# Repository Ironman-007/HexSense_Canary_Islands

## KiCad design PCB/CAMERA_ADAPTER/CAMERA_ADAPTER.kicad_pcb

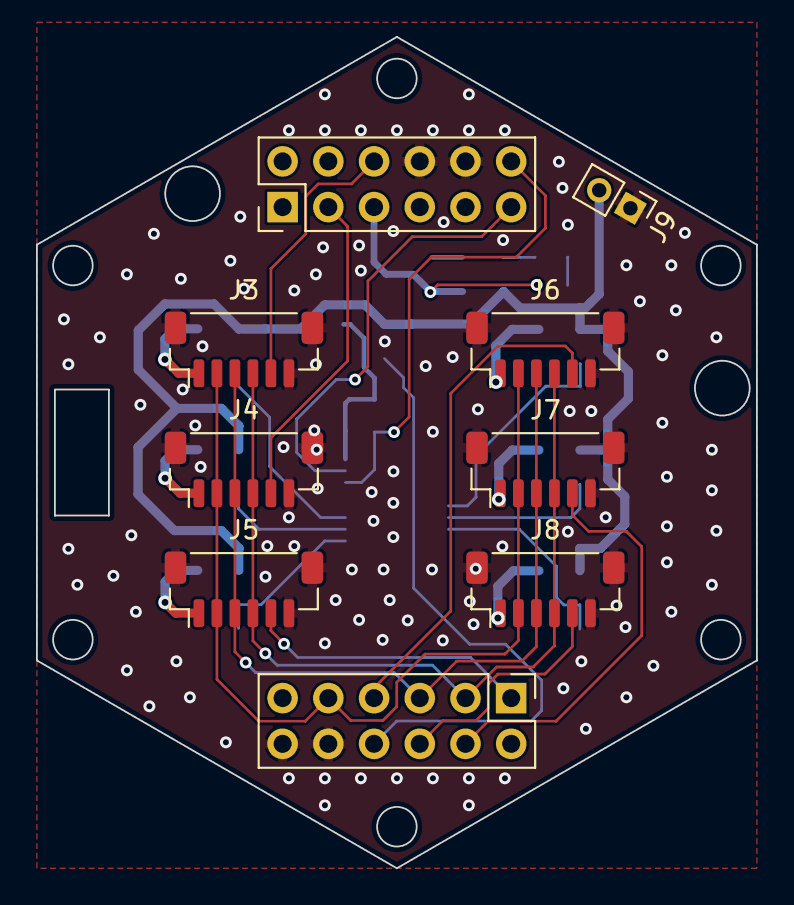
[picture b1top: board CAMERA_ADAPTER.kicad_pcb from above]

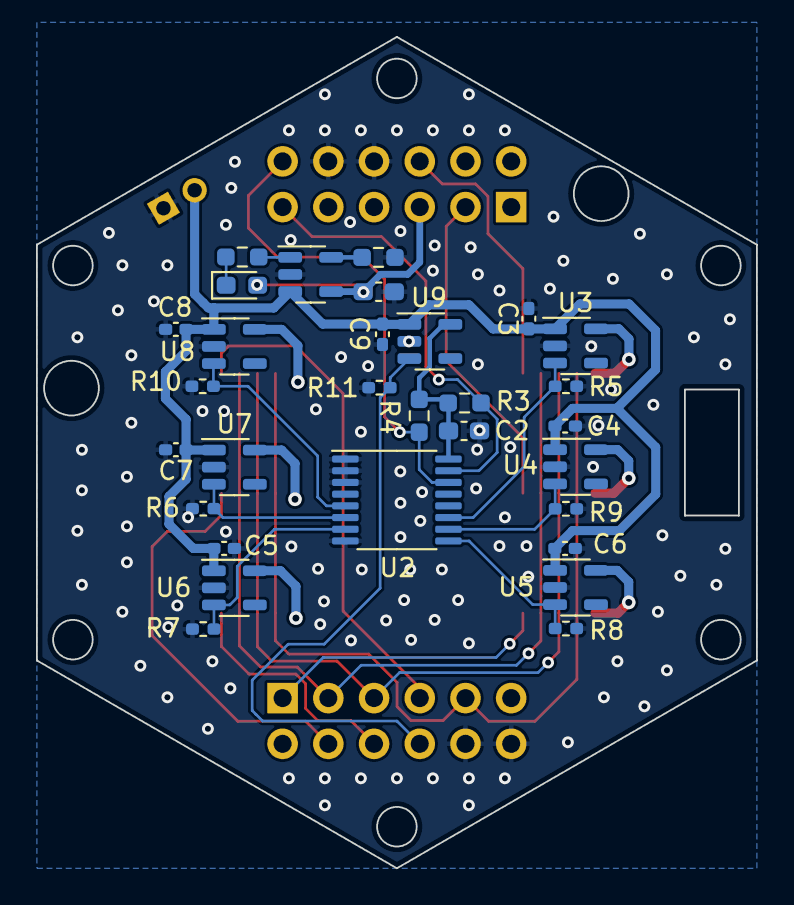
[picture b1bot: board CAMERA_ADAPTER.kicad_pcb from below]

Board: 2 copper layers, 40.0 x 46.2 mm, 39 parts (30 on the bottom side), 31 nets.

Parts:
C1, C2: 0.1uF; C_0603_1608Metric_Pad1.08x0.95mm_HandSolder
C3, C4, C5, C6, C7, C8, C9: 0.1uF; C_0402_1005Metric_Pad0.74x0.62mm_HandSolder
D1: RED; LED_0603_1608Metric_Pad1.05x0.95mm_HandSolder
J1, J2: Conn_02x06_Odd_Even; PinHeader_2x06_P2.54mm_Vertical
J3, J4, J5, J6, J7, J8: BM06B-SRSS-TBT(LF)(SN); JST_SH_BM06B-SRSS-TB_1x06-1MP_P1.00mm_Vertical
J9: Battery; PinHeader_1x02_P2.00mm_Vertical
R1: 10k; R_0603_1608Metric_Pad0.98x0.95mm_HandSolder
R2: 1k; R_0603_1608Metric_Pad0.98x0.95mm_HandSolder
R3, R4: NC; R_0603_1608Metric_Pad0.98x0.95mm_HandSolder
R5, R6, R7, R8, R9, R10, R11: 10k; R_0402_1005Metric_Pad0.72x0.64mm_HandSolder
U1: MCP73831-2-OT; SOT-23-5
U2: TCA9534; TSSOP-16_4.4x5mm_P0.65mm
U3, U4, U5, U6, U7, U8, U9: AP2112K-3.3; SOT-23-5

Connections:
+5V: C1.1, D1.2 (A), J1.5, U1.4 (VDD)
/A2: J1.6, J3.5
/A4: J2.8, R11.1, U9.3 (EN)
/A5: J1.3, J4.5
/CAM_BAT: C3.1, C4.1, C5.1, C6.1, C7.1, C8.1, C9.1, J9.2, U1.3 (VBAT), U3.1 (VIN), U4.1 (VIN), U5.1 (VIN), U6.1 (VIN), U7.1 (VIN), U8.1 (VIN), U9.1 (VIN)
/D1: J2.4, J7.5
/D2: J2.7, J6.5
/D3: J2.6, J8.5
/D12: J2.1, J5.5
/EN_1: R5.1, U2.11 (P6), U3.3 (EN)
/EN_2: R9.1, U2.10 (P5), U4.3 (EN)
/EN_3: R8.1, U2.9 (P4), U5.3 (EN)
/EN_4: R7.1, U2.7 (P3), U6.3 (EN)
/EN_5: R6.1, U2.6 (P2), U7.3 (EN)
/EN_6: R10.1, U2.5 (P1), U8.3 (EN)
/MISO: J2.9, J3.2, J4.2, J5.2, J6.2, J7.2, J8.2
/MOSI: J2.3, J3.4, J4.4, J5.4, J6.4, J7.4, J8.4
/SCK: J2.5, J3.3, J4.3, J5.3, J6.3, J7.3, J8.3
/SCL: J1.12, R4.2, U2.14 (SCL)
/SDA: J1.11, R3.2, U2.15 (SDA)
/V_CAM_1: J4.1, U4.5 (VOUT)
/V_CAM_2: J3.1, U3.5 (VOUT)
/V_CAM_3: J5.1, U5.5 (VOUT)
/V_CAM_4: J6.1, U8.5 (VOUT)
/V_CAM_5: J7.1, U7.5 (VOUT)
/V_CAM_6: J8.1, U6.5 (VOUT)
GND: C1.2, C2.2, C3.2, C4.2, C5.2, C6.2, C7.2, C8.2, C9.2, J1.8, J1.10, J2.10, J2.12, J3.6, J3.MP, J4.6, J4.MP, J5.6, J5.MP, J6.6, J6.MP, J7.6, J7.MP, J8.6, J8.MP, J9.1, R1.1, R5.2, R6.2, R7.2, R8.2, R9.2, R10.2, R11.2, U1.2 (VSS), U2.1 (A0), U2.2 (A1), U2.3 (A2), U2.8 (GND), U3.2 (GND), U4.2 (GND), U5.2 (GND), U6.2 (GND), U7.2 (GND), U8.2 (GND), U9.2 (GND)
unnamed: D1.1 (K), R2.2
unnamed: R1.2, U1.5 (PROG)
unnamed: R2.1, U1.1 (STAT)
VCC: C2.1, R3.1, R4.1, U2.16 (VDD), U9.5 (VOUT)

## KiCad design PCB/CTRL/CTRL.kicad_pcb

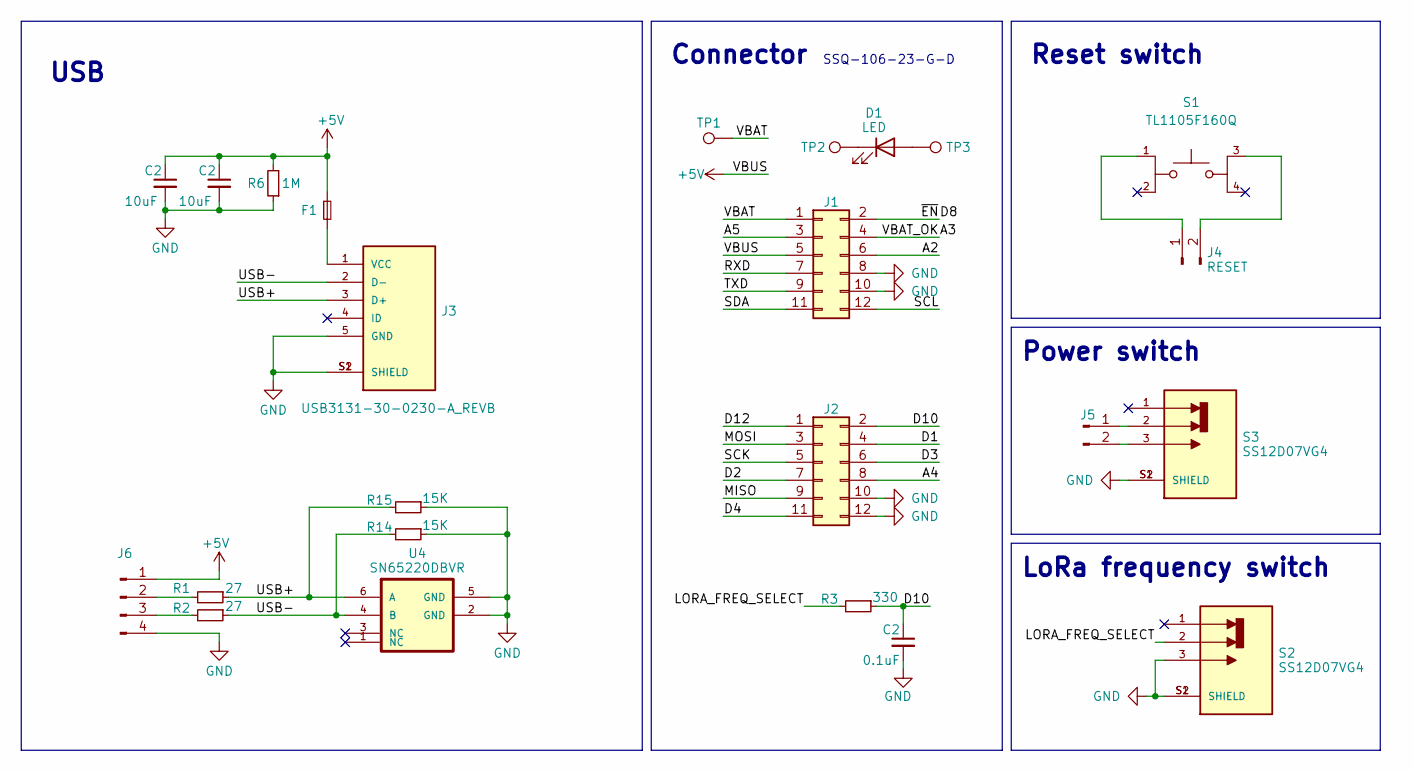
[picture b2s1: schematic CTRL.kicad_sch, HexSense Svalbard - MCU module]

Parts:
C2: 10uF; C_1206_3216Metric_Pad1.33x1.80mm_HandSolder
D1: LED; D_0603_1608Metric_Pad1.05x0.95mm_HandSolder
F1: Fuse_Small; Fuse_1206_3216Metric_Pad1.42x1.75mm_HandSolder
J1, J2: Conn_02x06_Odd_Even; PinHeader_2x06_P2.54mm_Vertical
J3: USB3131-30-0230-A_REVB; GCT_USB3131-30-0230-A_REVB; PARTREV B4
J4, J5: RESET; PinHeader_1x02_P2.00mm_Vertical
J6: Conn_01x04_Pin; PinHeader_1x04_P2.00mm_Vertical
R1, R2: 27; R_0402_1005Metric_Pad0.72x0.64mm_HandSolder
R3: 330; R_0402_1005Metric_Pad0.72x0.64mm_HandSolder
R6: 1M; R_0603_1608Metric_Pad0.98x0.95mm_HandSolder
R14, R15: 15K; R_0402_1005Metric_Pad0.72x0.64mm_HandSolder
S1: TL1105F160Q; SW_TL1105F160Q; PARTREV A
S2, S3: SS12D07VG4; SW_SS12D07VG4; PARTREV 1
TP1, TP2, TP3: TestPoint; TestPoint_Pad_1.5x1.5mm
U4: SN65220DBVR; SOT95P275X135-6N

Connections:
/A2: J1.6
/A3: J1.4
/A4: J2.8
/A5: J1.3
/D1: J2.4
/D2: J2.7
/D3: J2.6
/D4: J2.11
/D8: J1.2
/D12: J2.1
/LORA_FREQ_SELECT: R3.2, S2.2
/MISO: J2.9
/MOSI: J2.3
/RXD: J1.7
/SCK: J2.5
/SCL: J1.12
/SDA: J1.11
/TXD: J1.9
/USB+: J3.3 (D+), R1.1, R15.2, U4.6 (A)
/USB-: J3.2 (D-), R2.1, R14.2, U4.4 (B)
/VBAT: J1.1, TP1.1
GND: C2.2, J1.8, J1.10, J2.10, J2.12, J3.5 (GND), J3.S1 (SHIELD), J3.S2 (SHIELD), J6.4, R14.1, R15.1, S2.3, S2.S1 (SHIELD), S2.S2 (SHIELD), S3.S1 (SHIELD), S3.S2 (SHIELD), U4.2 (GND), U4.5 (GND); also elsewhere on the board
unnamed: D1.2 (A), TP3.1
unnamed: D1.1 (K), TP2.1
unnamed: F1.2, J3.1 (VCC)
unnamed: J4.1, S1.1
unnamed: J4.2, S1.3
unnamed: J5.1, S3.2
unnamed: J5.2, S3.3
unnamed: J6.2, R1.2
unnamed: J6.3, R2.2

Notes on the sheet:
Reset switch
LoRa frequency switch
USB
Connector
SSQ-106-23-G-D
Power switch

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
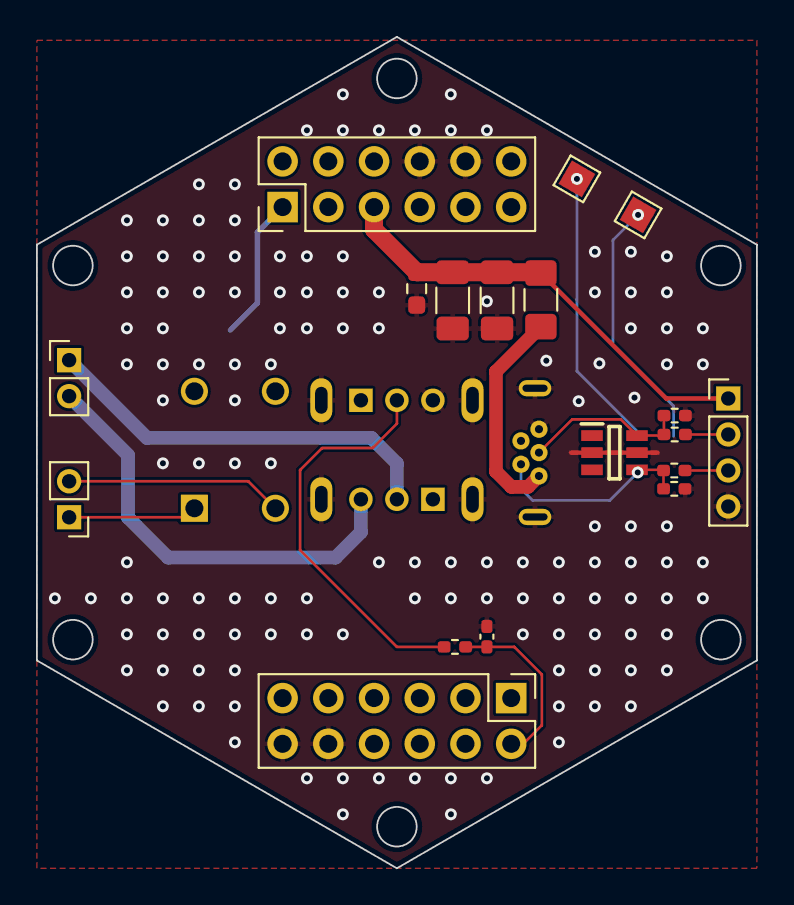
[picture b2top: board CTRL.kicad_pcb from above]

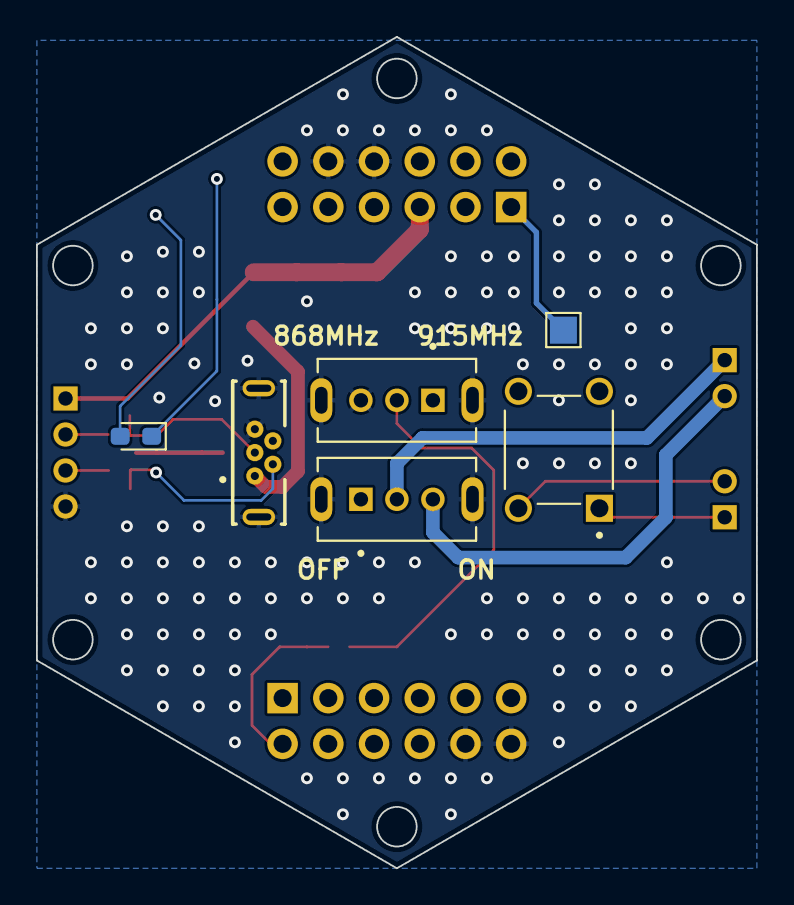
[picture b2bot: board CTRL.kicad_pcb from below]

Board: 2 copper layers, 40.0 x 46.2 mm, 24 parts (6 on the bottom side), 16 nets.

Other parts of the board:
C3: 10uF; C_1206_3216Metric_Pad1.33x1.80mm_HandSolder
C4: 0.1uF; C_0402_1005Metric_Pad0.74x0.62mm_HandSolder
R4: 1M; R_0603_1608Metric_Pad0.98x0.95mm_HandSolder

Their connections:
GND: C3.2, C4.2, R4.1; also elsewhere on the board

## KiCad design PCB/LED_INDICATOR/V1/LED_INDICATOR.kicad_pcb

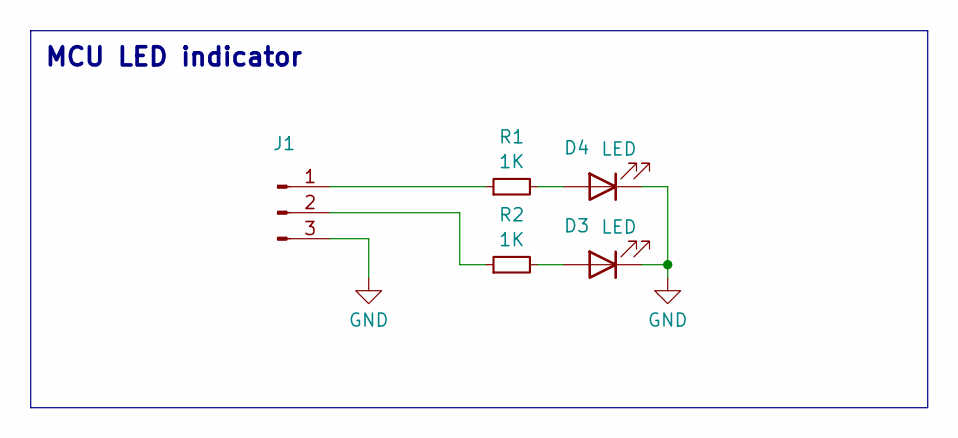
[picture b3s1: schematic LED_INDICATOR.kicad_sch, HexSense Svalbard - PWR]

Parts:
D3, D4: LED; LED_1206_3216Metric_Pad1.42x1.75mm_HandSolder
J1: Conn_01x03_Pin; Harwin_M20-89003xx_1x03_P2.54mm_Horizontal
R1, R2: 1K; R_1206_3216Metric_Pad1.30x1.75mm_HandSolder

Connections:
GND: D3.1 (K), D4.1 (K), J1.3
unnamed: D3.2 (A), R2.2
unnamed: D4.2 (A), R1.2
unnamed: J1.1, R1.1
unnamed: J1.2, R2.1

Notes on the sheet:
MCU LED indicator

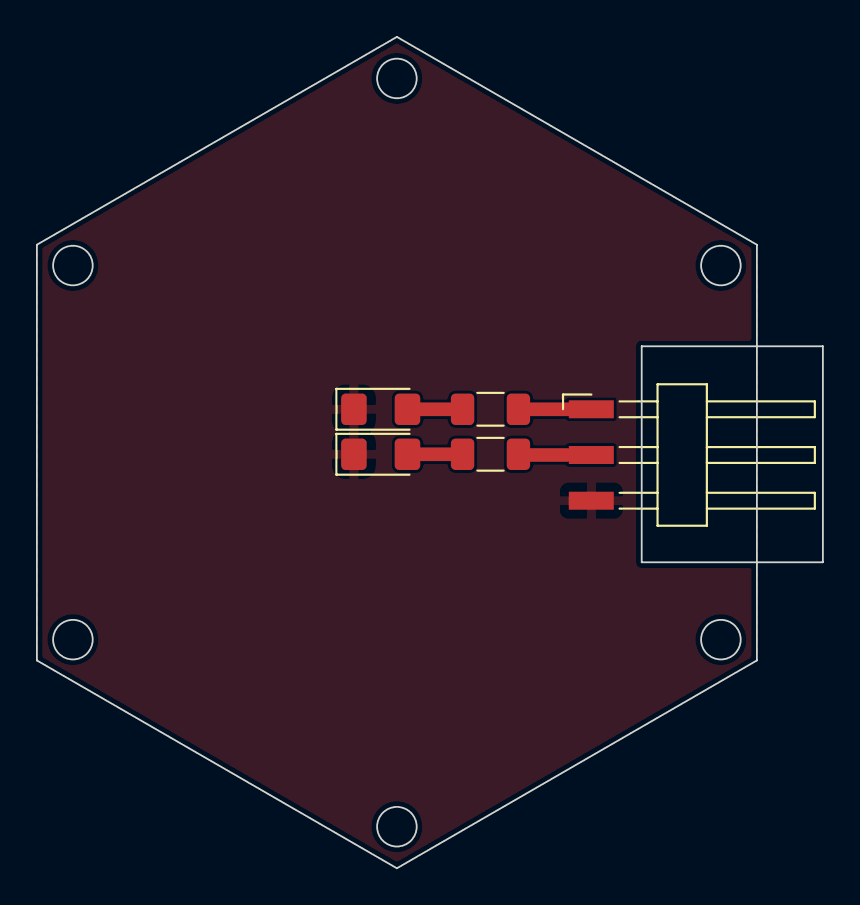
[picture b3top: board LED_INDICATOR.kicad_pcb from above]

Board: 2 copper layers, 43.7 x 46.2 mm, 5 parts (0 on the bottom side), 5 nets.

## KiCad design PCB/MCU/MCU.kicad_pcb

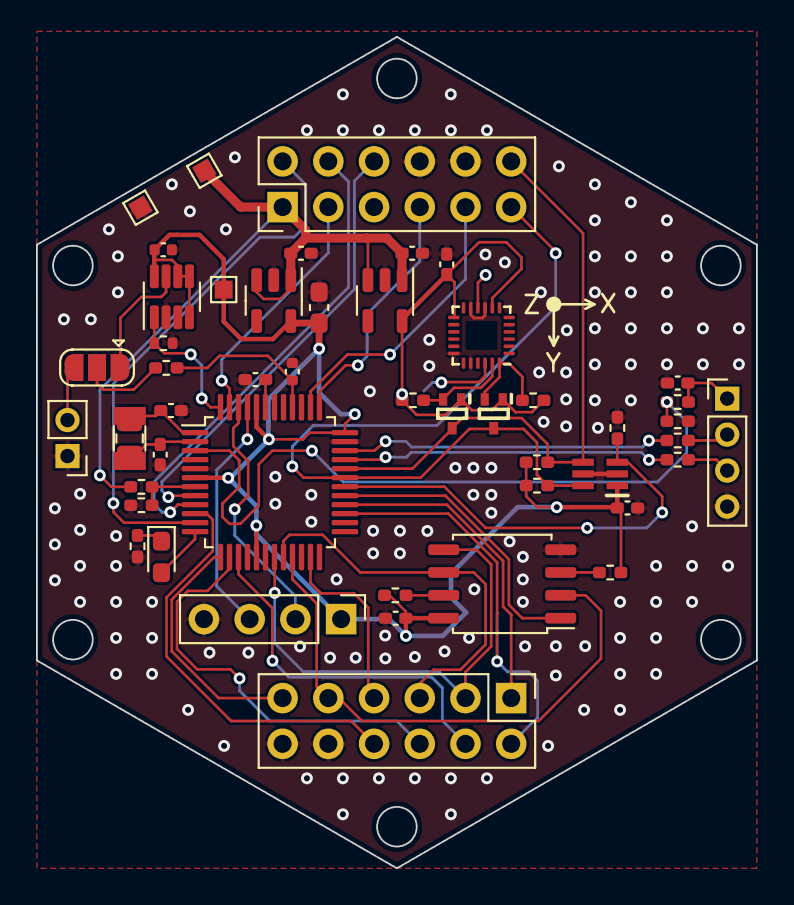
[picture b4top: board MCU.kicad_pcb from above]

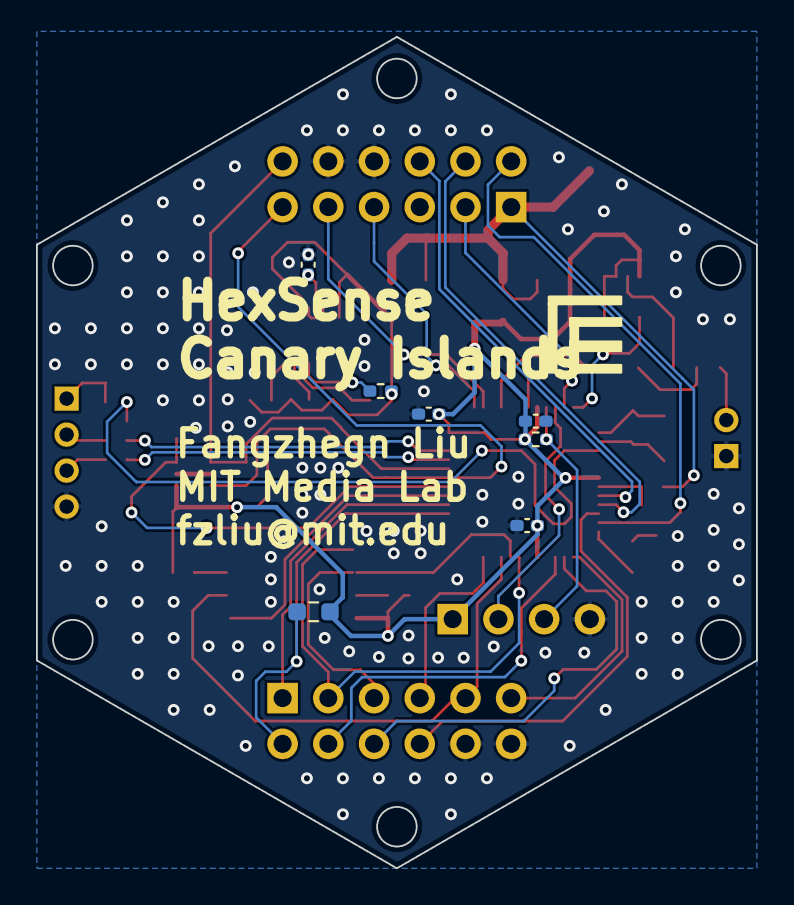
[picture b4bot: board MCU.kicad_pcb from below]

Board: 2 copper layers, 40.0 x 46.2 mm, 56 parts (7 on the bottom side), 49 nets.

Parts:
C1, C3, C7: 0.01uF; C_0402_1005Metric_Pad0.74x0.62mm_HandSolder
C2, C4: 18pF; C_0402_1005Metric_Pad0.74x0.62mm_HandSolder
C5, C12: 1uF; C_0402_1005Metric_Pad0.74x0.62mm_HandSolder
C6, C8, C11, C14, C15, C16: 0.1uF; C_0402_1005Metric_Pad0.74x0.62mm_HandSolder
C9: 10uF; C_0603_1608Metric_Pad1.08x0.95mm_HandSolder
C10: 0.1uF; C_0402_1005Metric
C13: 10pF; C_0402_1005Metric
D1: RED; LED_0603_1608Metric_Pad1.05x0.95mm_HandSolder
IC2: LTC4311CSC6#TRPBF; SOT65P210X100-6N
J1, J2: Conn_02x06_Odd_Even; PinHeader_2x06_P2.54mm_Vertical
J4: Conn_01x04_Pin; PinHeader_1x04_P2.54mm_Vertical
J5: RESET; PinHeader_1x02_P2.00mm_Vertical
J6: Conn_01x04_Pin; PinHeader_1x04_P2.00mm_Vertical
JP1: RST Jumper; SolderJumper-3_P1.3mm_Open_RoundedPad1.0x1.5mm
Q1, Q2: PJE8408_R1_00001; SOTFL50P160X60-3N
R1, R2: 4.7K; R_0402_1005Metric_Pad0.72x0.64mm_HandSolder
R3, R12, R13, R17, R18, R21: 10K; R_0402_1005Metric_Pad0.72x0.64mm_HandSolder
R4: 10K; R_0402_1005Metric
R5, R6: 27; R_0402_1005Metric_Pad0.72x0.64mm_HandSolder
R7, R8, R14, R15: 499K; R_0402_1005Metric_Pad0.72x0.64mm_HandSolder
R9, R11: 330; R_0402_1005Metric_Pad0.72x0.64mm_HandSolder
R10: 10k; R_0402_1005Metric_Pad0.72x0.64mm_HandSolder
R19: PH; R_0805_2012Metric_Pad1.20x1.40mm_HandSolder
R20: 10K; R_0603_1608Metric_Pad0.98x0.95mm_HandSolder
TP1, TP2, TP3: BAT_TP; TestPoint_Pad_1.0x1.0mm
U1: MB85RS2MTAPNF-G-BDERE1; SSOP-8_5.25x5.24mm_P1.27mm
U2: ATSAMD21G18A-A; TQFP-48_7x7mm_P0.5mm
U3: MAX6372; SOT-23-8
U4: ADP160AUJZ-3.3-R7; TSOT-23-5
U5: ICM-20948; InvenSense_QFN-24_3x3mm_P0.4mm
U6: ADP160AUJZ-1.8; TSOT-23-5
Y1: 32KHz; Crystal_SMD_3215-2Pin_3.2x1.5mm

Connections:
+1V8: C11.1, Q1.1, Q2.1, R17.2, R18.2, R21.2, U5.8 (VDDIO), U5.13 (VDD), U6.5 (VOUT)
+5V: C7.1, J6.1, R14.1
/A0: R14.2, R15.1, U2.3 (PA02)
/A1: R7.2, R8.1, U2.7 (PB08)
/A2: J1.6, U2.8 (PB09)
/A3: J1.4, U2.9 (PA04)
/A4: J2.8, U2.10 (PA05)
/A5: J1.3, U2.47 (PB02)
/D1: J2.4, U2.15 (PA10)
/D2: J2.7, U2.23 (PA14)
/D3: J2.6, U2.14 (PA09)
/D4: J2.11, U2.13 (PA08)
/D6: U1.1 (~CS), U2.29 (PA20)
/D7: IC2.3 (ENABLE), R3.2, U2.30 (PA21)
/D8: J1.2, U2.11 (PA06)
/D9: D1.2 (A), U2.12 (PA07)
/D10: J2.2, R20.2, U2.27 (PA18)
/D12: J2.1, U2.28 (PA19)
/MISO: J2.9, U1.2 (SO), U2.21 (PA12)
/MOSI: J2.3, U1.5 (SI), U2.19 (PB10)
/RXD: J1.7, U2.37 (PB22)
/RXLED: R4.1, U2.48 (PB03), U3.1 (WDI)
/SCK: J2.5, U1.6 (SCK), U2.20 (PB11)
/SCL: IC2.4 (BUS2), J1.12, Q2.3, R1.1, U2.32 (PA23)
/SCL_1V8: Q2.2, R17.1, U5.23 (SCL/SCLK)
/SDA: IC2.6 (BUS1), J1.11, Q1.3, R2.1, U2.31 (PA22)
/SDA_1V8: Q1.2, R18.1, U5.24 (SDA/SDI)
/SWDCLK: J4.3, R10.1, U2.45 (PA30)
/SWDIO: J4.2, U2.46 (PA31)
/TXD: J1.9, U2.38 (PB23)
/USB+: R5.1, U2.34 (PA25)
/USB-: R6.1, U2.33 (PA24)
/VBAT: C8.1, C14.1, J1.1, R7.1, TP3.1, U4.1 (VIN), U4.3 (EN), U6.1 (VIN), U6.3 (EN)
/~RESET: C13.1, R9.2, U2.40 (~RESET)
GND: C1.2, C2.1, C3.2, C4.1, C5.1, C6.1, C7.2, C8.2, C9.1, C10.2, C11.2, C12.1, C13.2, C14.2, C15.1, C16.2, IC2.2 (GND_1), IC2.5 (GND_2), J1.8, J1.10, J2.10, J2.12, J4.4, J5.1, J6.4, R3.1, R4.2, R8.2, R11.2, R15.2, TP2.1, U1.4 (GND), U2.5 (GNDANA), U2.18 (GND), U2.35 (GND), U2.42 (GND), U3.2 (GND), U4.2 (GND), U5.9 (AD0/SDO), U5.11 (FSYNC), U5.18 (GND), U5.20 (RESV_20), U6.2 (GND)
unnamed: D1.1 (K), R11.1
unnamed: J5.2, JP1.3 (B)
unnamed: J6.2, R5.2
unnamed: J6.3, R6.2
unnamed: JP1.1 (A), U3.7 (~WDO)
unnamed: JP1.2 (C), R9.1
unnamed: R12.1, U1.7 (~HOLD)
unnamed: R13.1, U1.3 (~WP)
unnamed: C2.2, R19.2, U2.1 (PA00), Y1.2
unnamed: C4.2, R19.1, U2.2 (PA01), Y1.1
unnamed: C12.2, U2.43 (VDDCORE)
unnamed: C16.1, U5.10 (REGOUT)
unnamed: R21.1, U5.22 (~CS)
VCC: C1.1, C3.1, C5.2, C6.2, C9.2, C10.1, C15.2, IC2.1 (VCC), J4.1, R1.2, R2.2, R10.2, R12.2, R13.2, R20.1, TP1.1, U1.8 (VDD), U2.6 (VDDANA), U2.17 (VDDIO), U2.36 (VDDIO), U2.44 (VDDIN), U3.4 (SET0), U3.5 (SET1), U3.6 (SET2), U3.8 (VCC), U4.5 (VOUT)

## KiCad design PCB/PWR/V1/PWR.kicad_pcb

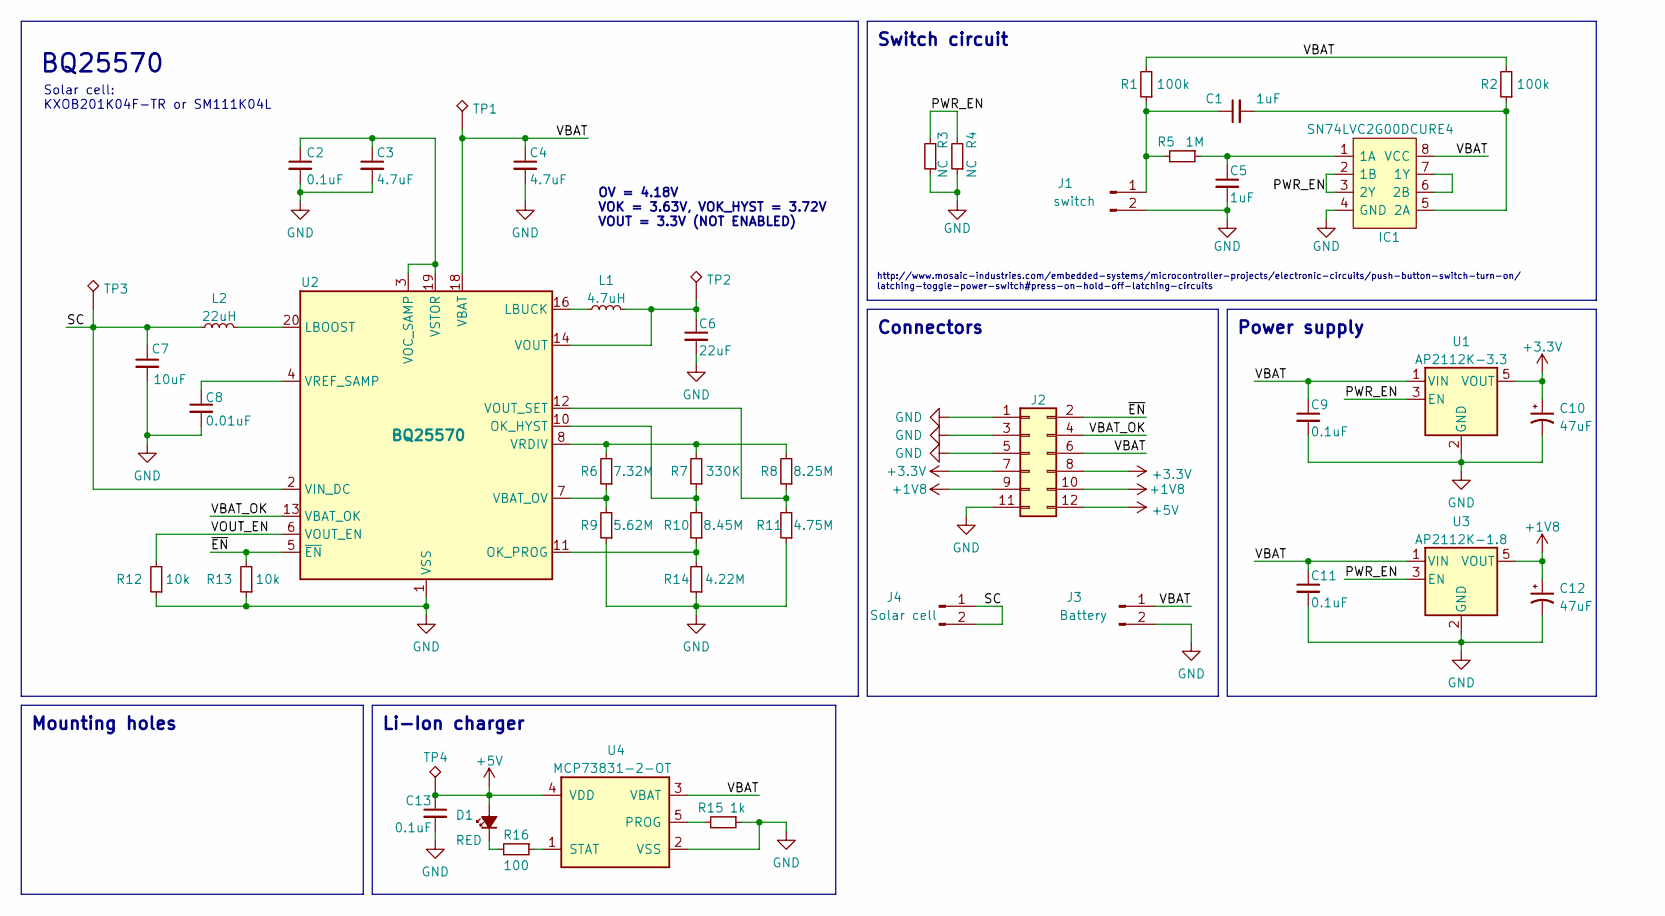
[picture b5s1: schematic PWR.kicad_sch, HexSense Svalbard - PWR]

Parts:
C1, C5: 1uF; C_0402_1005Metric_Pad0.74x0.62mm_HandSolder
C2, C9, C11, C13: 0.1uF; C_0402_1005Metric_Pad0.74x0.62mm_HandSolder
C3, C4: 4.7uF; C_0603_1608Metric_Pad1.08x0.95mm_HandSolder
C6: 22uF; C_0805_2012Metric_Pad1.18x1.45mm_HandSolder
C7: 10uF; C_0603_1608Metric_Pad1.08x0.95mm_HandSolder
C8: 0.01uF; C_0402_1005Metric_Pad0.74x0.62mm_HandSolder
C10, C12: 47uF; LED_0805_2012Metric_Pad1.15x1.40mm_HandSolder
D1: RED; LED_0603_1608Metric_Pad1.05x0.95mm_HandSolder
IC1: SN74LVC2G00DCURE4; SOP50P310X90-8N; Manufacturer_Part_Number SN74LVC2G00DCURE4
J1: switch; PinHeader_1x02_P2.54mm_Vertical
J2: Conn_02x06_Odd_Even; PinHeader_2x06_P2.54mm_Vertical
J3: Battery; PinHeader_2x01_P2.00mm_Vertical
J4: Solar cell; PinHeader_2x01_P2.00mm_Vertical
L1: 4.7uH; L_Wuerth_MAPI-3015
L2: 22uH; L_Taiyo-Yuden_NR-40xx_HandSoldering
R1, R2: 100k; R_0402_1005Metric_Pad0.72x0.64mm_HandSolder
R3, R4: NC; R_0402_1005Metric_Pad0.72x0.64mm_HandSolder
R5: 1M; R_0603_1608Metric_Pad0.98x0.95mm_HandSolder
R6: 7.32M; R_0603_1608Metric_Pad0.98x0.95mm_HandSolder
R7: 330K; R_0603_1608Metric_Pad0.98x0.95mm_HandSolder
R8: 8.25M; R_0603_1608Metric_Pad0.98x0.95mm_HandSolder
R9: 5.62M; R_0603_1608Metric_Pad0.98x0.95mm_HandSolder
R10: 8.45M; R_0603_1608Metric_Pad0.98x0.95mm_HandSolder
R11: 4.75M; R_0603_1608Metric_Pad0.98x0.95mm_HandSolder
R12, R13: 10k; R_0603_1608Metric_Pad0.98x0.95mm_HandSolder
R14: 4.22M; R_0603_1608Metric_Pad0.98x0.95mm_HandSolder
R15: 1k; R_0603_1608Metric_Pad0.98x0.95mm_HandSolder
R16: 100; R_0603_1608Metric_Pad0.98x0.95mm_HandSolder
TP1, TP2, TP3, TP4: TestPoint_Alt; TestPoint_Pad_1.0x1.0mm
U1: AP2112K-3.3; SOT-23-5
U2: BQ25570; QFN-20-1EP_3.5x3.5mm_P0.5mm_EP2x2mm
U3: AP2112K-1.8; SOT-23-5
U4: MCP73831-2-OT; SOT-23-5

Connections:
+1V8: C12.1, J2.9, J2.10, U3.5 (VOUT)
+3V3: C10.1, J2.7, J2.8, U1.5 (VOUT)
+5V: C13.1, D1.2 (A), J2.12, TP4.1, U4.4 (VDD)
/PWR_EN: IC1.2 (1B), IC1.3 (2Y), R3.2, R4.2, U1.3 (EN), U3.3 (EN)
/SC: C7.1, J4.1, J4.2, L2.1, TP3.1, U2.2 (VIN_DC)
/VBAT: C4.1, C9.1, C11.1, IC1.8 (VCC), J2.6, J3.1, R1.2, R2.2, TP1.1, U1.1 (VIN), U2.18 (VBAT), U3.1 (VIN), U4.3 (VBAT)
/VBAT_OK: J2.4, U2.13 (VBAT_OK)
/VOUT_EN: R12.2, U2.6 (VOUT_EN)
/~EN: J2.2, R13.2, U2.5 (~EN)
GND: C2.2, C3.2, C4.2, C5.2, C6.2, C7.2, C8.2, C9.2, C10.2, C11.2, C12.2, C13.2, IC1.4 (GND), J1.2, J2.1, J2.3, J2.5, J2.11, J3.2, R3.1, R4.1, R9.1, R11.1, R12.1, R13.1, R14.1, R15.1, U1.2 (GND), U2.1 (VSS), U2.9 (VSS), U2.15 (VSS), U2.17 (VSS), U2.21 (VSS), U3.2 (GND), U4.2 (VSS)
unnamed: D1.1 (K), R16.2
unnamed: C5.1, IC1.1 (1A), R5.1
unnamed: IC1.6 (2B), IC1.7 (1Y)
unnamed: C1.2, IC1.5 (2A), R2.1
unnamed: C1.1, J1.1, R1.1, R5.2
unnamed: L2.2, U2.20 (LBOOST)
unnamed: L1.1, U2.16 (LBUCK)
unnamed: R7.1, R10.2, U2.10 (OK_HYST)
unnamed: R10.1, R14.2, U2.11 (OK_PROG)
unnamed: R6.1, R9.2, U2.7 (VBAT_OV)
unnamed: C2.1, C3.1, U2.3 (VOC_SAMP), U2.19 (VSTOR)
unnamed: C6.1, L1.2, TP2.1, U2.14 (VOUT)
unnamed: R8.1, R11.2, U2.12 (VOUT_SET)
unnamed: R6.2, R7.2, R8.2, U2.8 (VRDIV)
unnamed: C8.1, U2.4 (VREF_SAMP)
unnamed: R15.2, U4.5 (PROG)
unnamed: R16.1, U4.1 (STAT)

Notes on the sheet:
Li-Ion charger
BQ25570
Switch circuit
Mounting holes
Solar cell: KXOB201K04F-TR or SM111K04L
OV = 4.18V VOK = 3.63V, VOK_HYST = 3.72V VOUT = 3.3V (NOT ENABLED)
Power supply
http://www.mosaic-industries.com/embedded-systems/microcontroller-projects/electronic-circuits/push-button-switch-turn-on/ latching-toggle-power-switch#press-on-hold-off-latching-circuits
Connectors

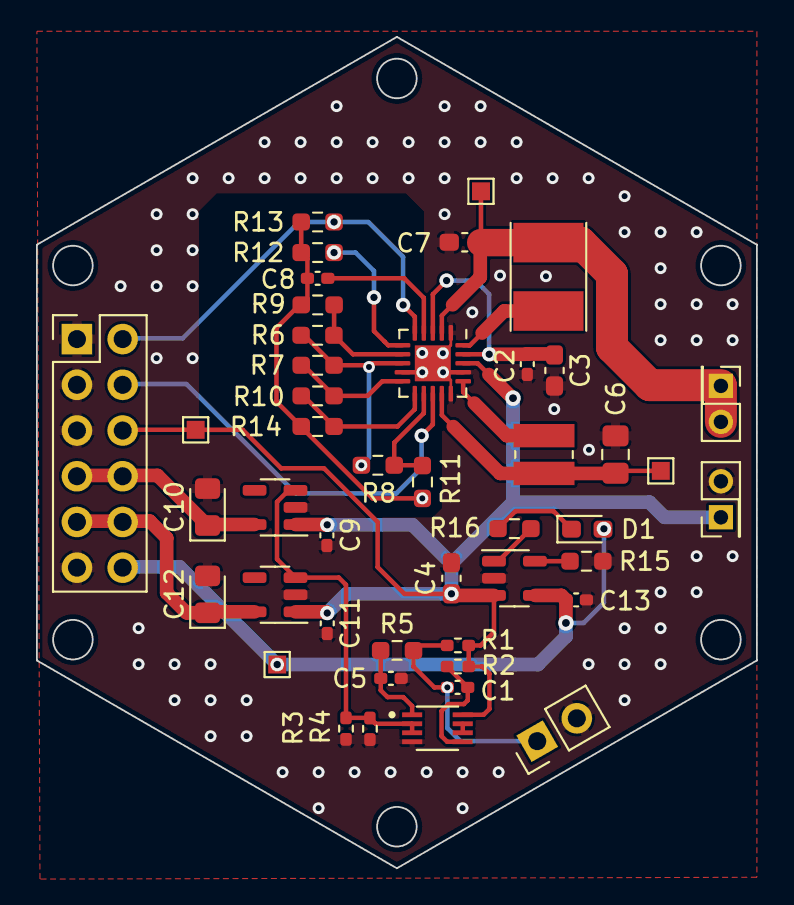
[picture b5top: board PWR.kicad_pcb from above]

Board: 2 copper layers, 40.0 x 46.2 mm, 45 parts (0 on the bottom side), 27 nets.

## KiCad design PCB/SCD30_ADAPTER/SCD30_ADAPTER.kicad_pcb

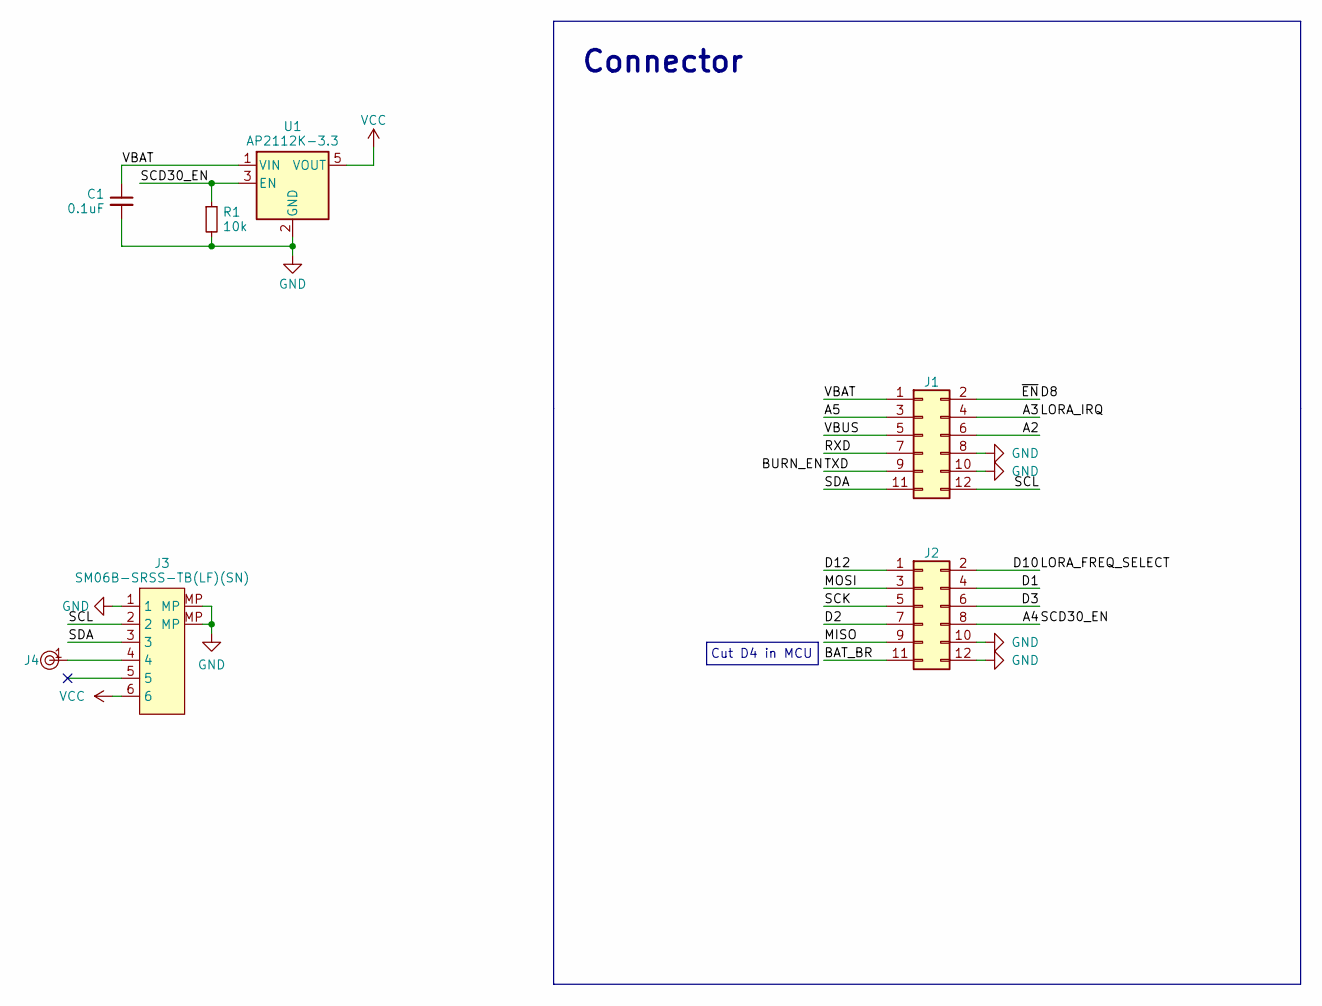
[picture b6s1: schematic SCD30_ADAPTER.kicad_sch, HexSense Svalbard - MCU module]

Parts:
C1: 0.1uF; C_0402_1005Metric_Pad0.74x0.62mm_HandSolder
J1, J2: Conn_02x06_Odd_Even; PinHeader_2x06_P2.54mm_Vertical
J3: SM06B-SRSS-TB(LF)(SN); JST_SH_SM06B-SRSS-TB_1x06-1MP_P1.00mm_Horizontal
J4: pin; PinHeader_1x01_P2.00mm_Vertical
R1: 10k; R_0402_1005Metric_Pad0.72x0.64mm_HandSolder
U1: AP2112K-3.3; SOT-23-5

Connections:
/A2: J1.6
/A3: J1.4
/A4: J2.8, R1.1, U1.3 (EN)
/A5: J1.3
/BAT_BR: J2.11
/BURN_EN: J1.9
/D1: J2.4
/D2: J2.7
/D3: J2.6
/D8: J1.2
/D10: J2.2
/D12: J2.1
/MISO: J2.9
/MOSI: J2.3
/RXD: J1.7
/SCK: J2.5
/SCL: J1.12, J3.2
/SDA: J1.11, J3.3
/VBAT: C1.1, J1.1, U1.1 (VIN)
/VBUS: J1.5
GND: C1.2, J1.8, J1.10, J2.10, J2.12, J3.1, J3.MP, R1.2, U1.2 (GND)
unnamed: J3.4, J4.1
VCC: J3.6, U1.5 (VOUT)

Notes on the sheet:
Connector
Cut D4 in MCU

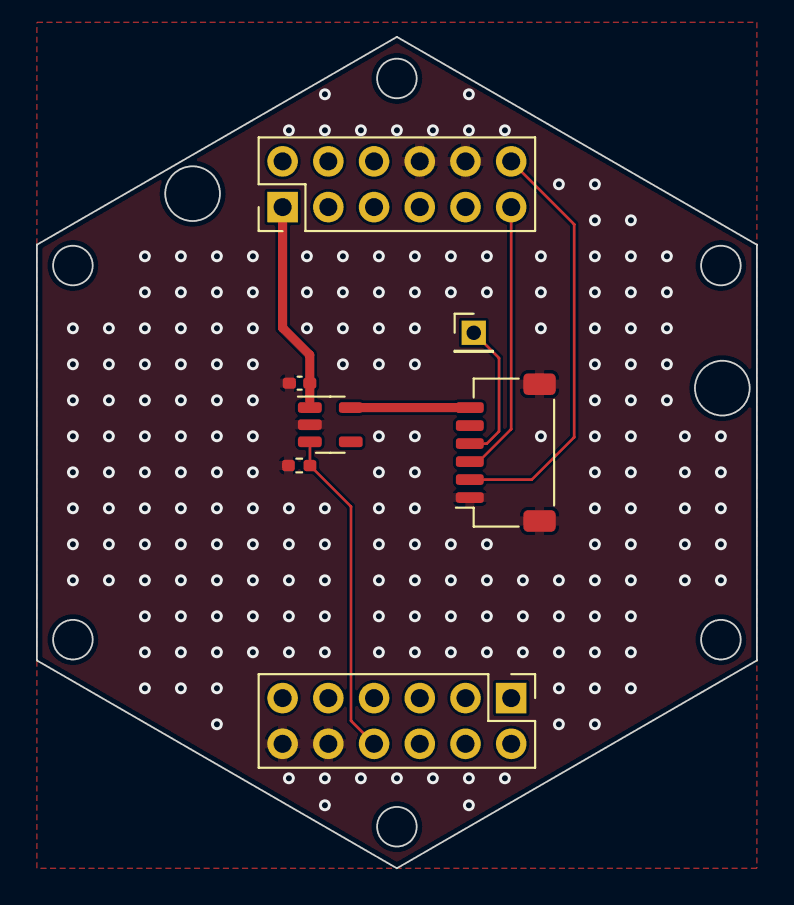
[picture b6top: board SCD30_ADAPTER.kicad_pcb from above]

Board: 2 copper layers, 40.0 x 46.2 mm, 7 parts (0 on the bottom side), 7 nets.

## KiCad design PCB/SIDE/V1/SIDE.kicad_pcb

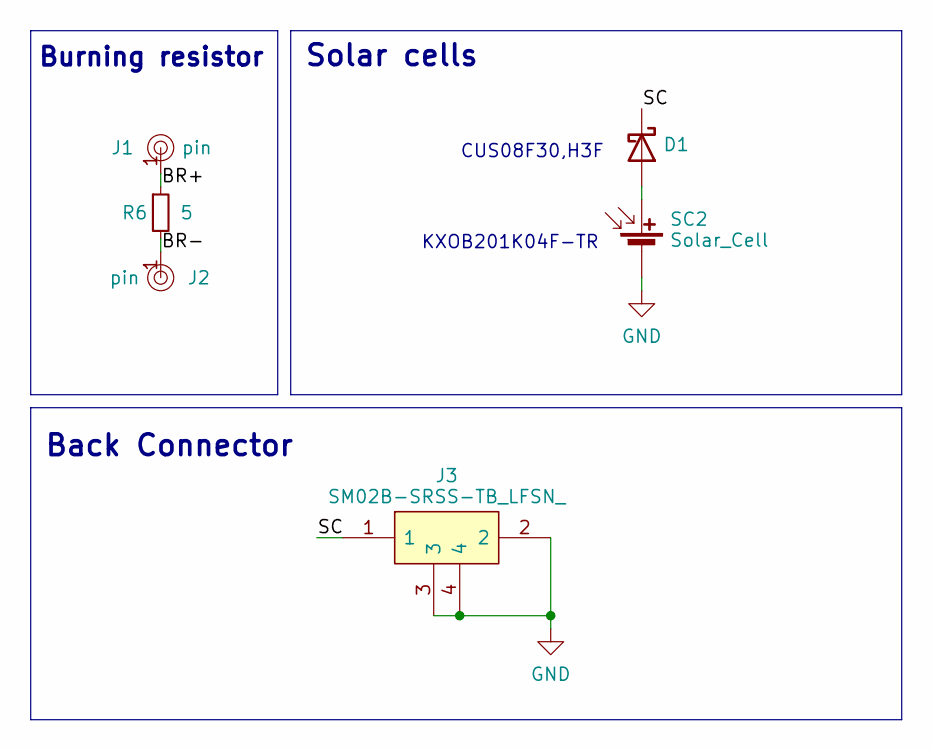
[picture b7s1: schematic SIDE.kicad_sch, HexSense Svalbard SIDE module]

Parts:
D1: D_Schottky; D_0805_2012Metric_Pad1.15x1.40mm_HandSolder
J1, J2: pin; 1_pin_SMD_1mmx1mm
J3: SM02B-SRSS-TB_LFSN_; SM02B-SRSS-TB; Manufacturer_Part_Number SM02B-SRSS-TB(LFSN)
R6: 5; R_Axial_DIN0207_L6.3mm_D2.5mm_P10.16mm_Horizontal
SC2: Solar_Cell; KXOB201K04F-TR

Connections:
/BR+: J1.1, R6.1
/BR-: J2.1, R6.2
/SC: D1.1 (K), J3.1
GND: J3.2, J3.3, J3.4, SC2.2 (-)
unnamed: D1.2 (A), SC2.1 (+)

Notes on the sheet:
Burning resistor
Back Connector
KXOB201K04F-TR
Solar cells
CUS08F30,H3F

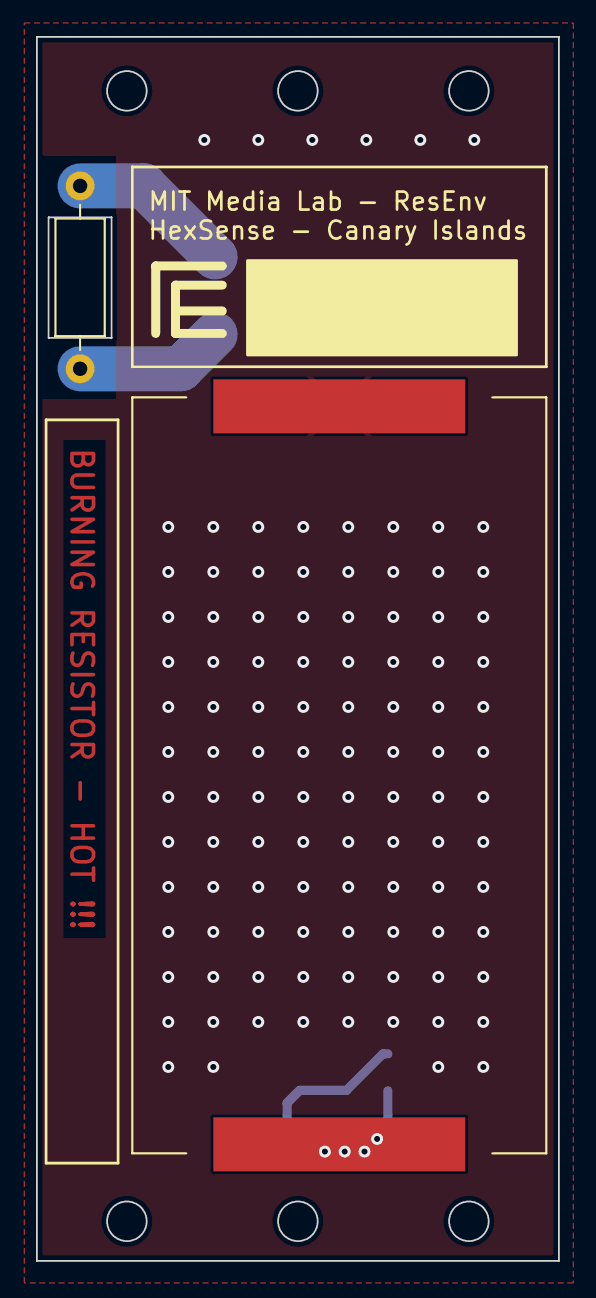
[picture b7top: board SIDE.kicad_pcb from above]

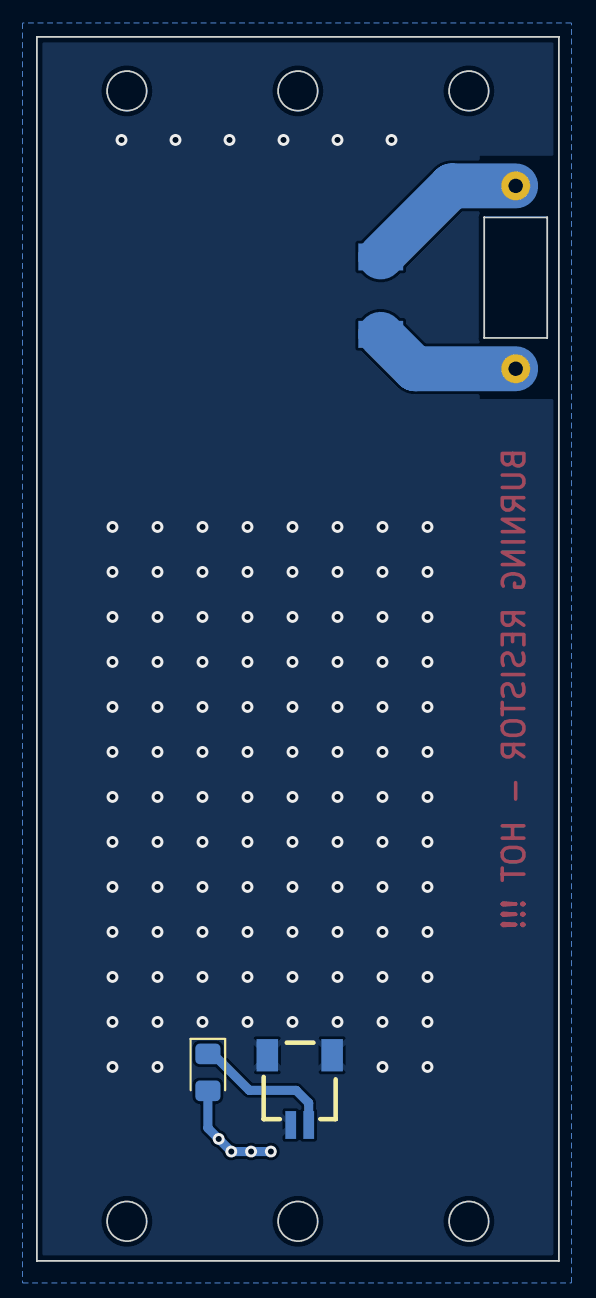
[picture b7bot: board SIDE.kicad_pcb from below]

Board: 2 copper layers, 29.0 x 68.0 mm, 6 parts (4 on the bottom side), 5 nets.
